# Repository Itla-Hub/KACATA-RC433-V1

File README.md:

# KACATA-RC433-V1
KACATA-RC433-V1 es un control remoto a 433Mhz
MCU MKE04Z128VQH4

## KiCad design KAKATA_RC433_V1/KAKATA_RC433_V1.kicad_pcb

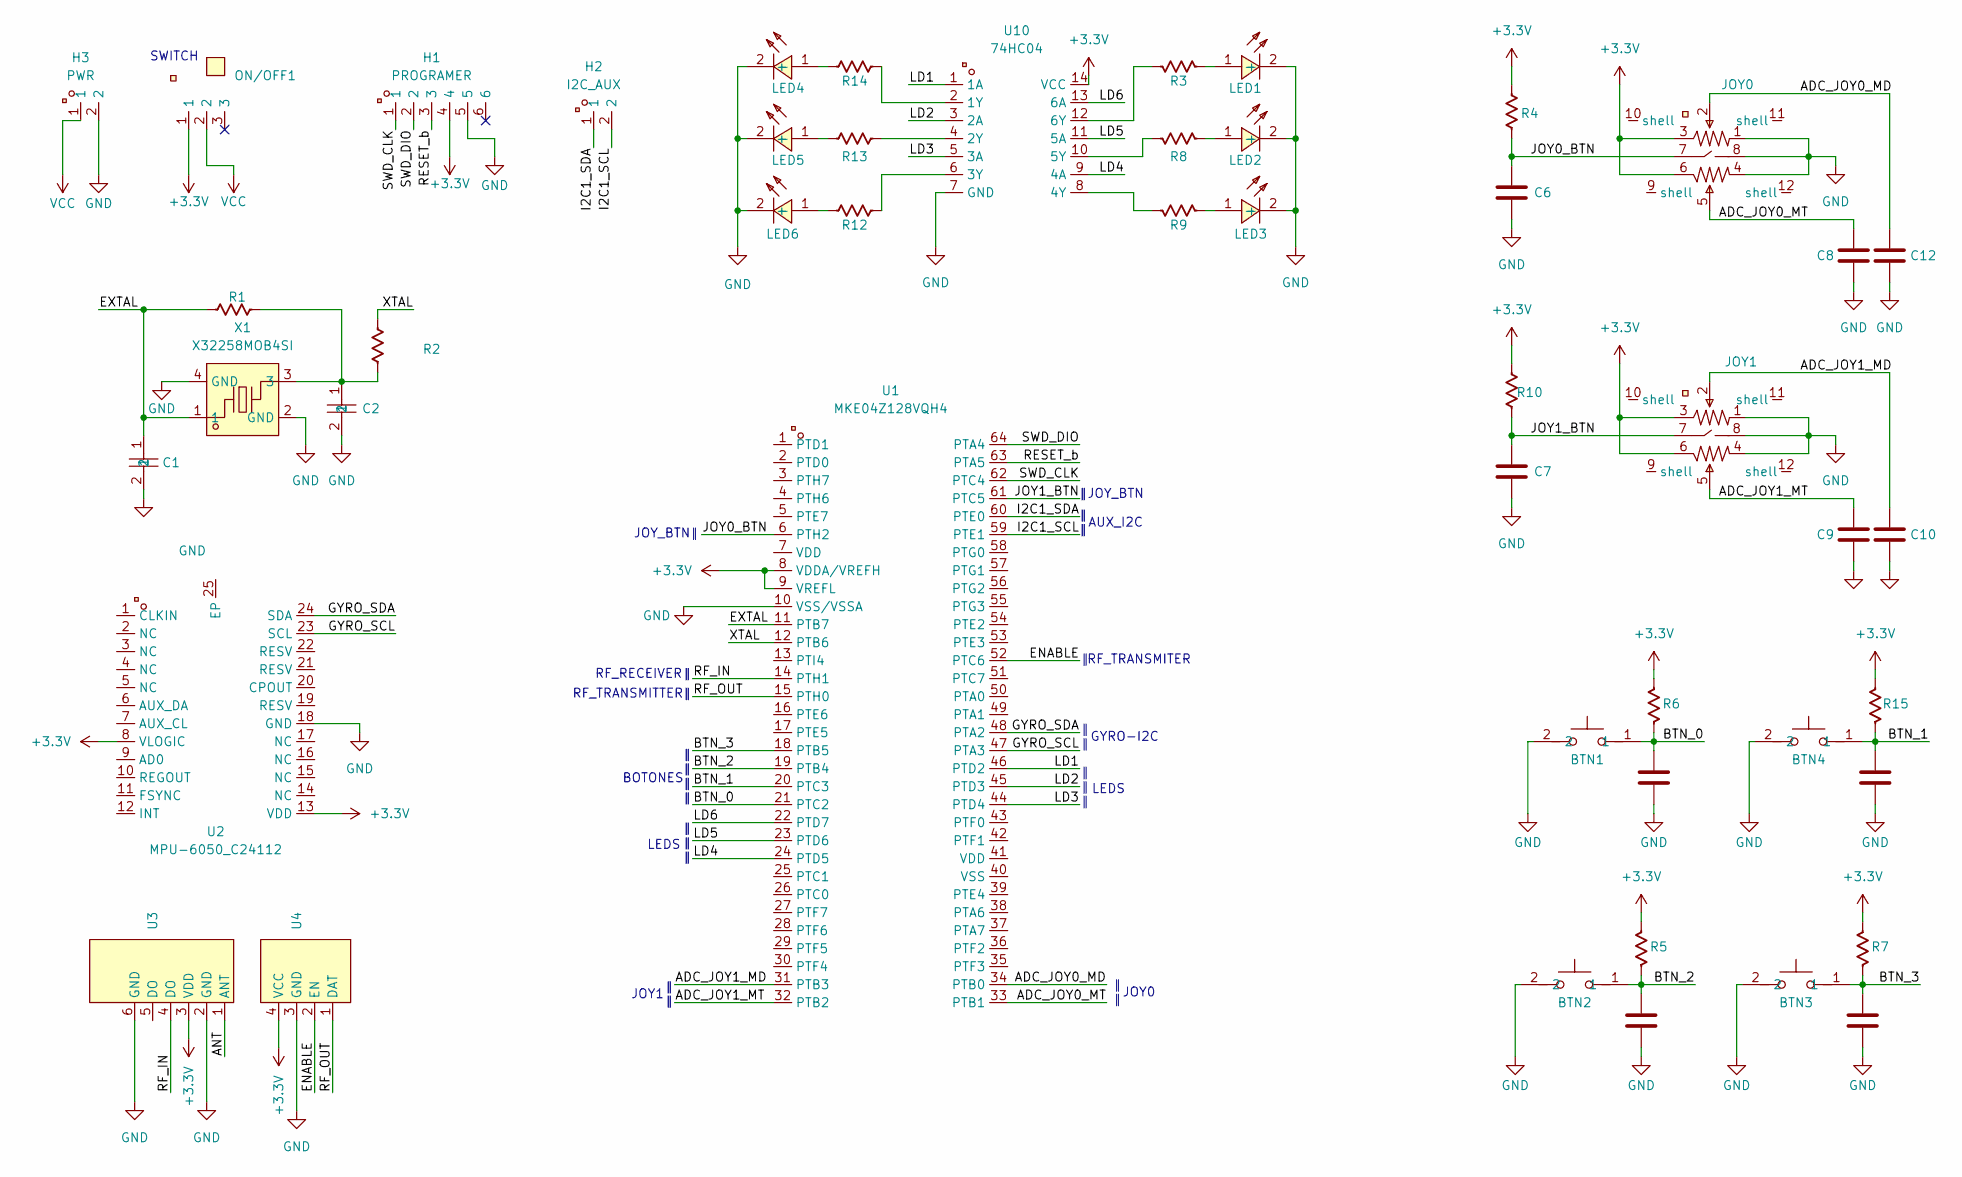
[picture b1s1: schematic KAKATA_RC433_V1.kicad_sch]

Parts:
BTN1, BTN2, BTN3, BTN4: CPG151101D01; SW-TH_CPG151101D9X; LCSC Part C49234238
C1, C2: CL10C120JB8NNNC; C0603; LCSC Part C38523
C3, C4, C5, C6, C7, C8, C9, C10, C11, C12: C_0603; C_0603_1608Metric
H1: PROGRAMER; HDR-TH_6P-P2.54-V-M; LCSC Part C42431790
H2: I2C_AUX; HDR-TH_2P-P2.54-V-M; LCSC Part C42431820
H3: PWR; HDR-TH_2P-P2.54-V-M; LCSC Part C42431820
JOY0, JOY1: YF16S-FL7.2-B5KB(45-10)-Y; JOYTICK-TH_YF16S-FL7.2-B5KB-45-10-Y_1; LCSC Part C37323740
LED1, LED2, LED3, LED4, LED5, LED6: YLED0603R; LED0603-FD; LCSC Part C19171390
ON/OFF1: MT-0-123-D001-D000-LF; SW-TH_3P-L13.1-W8.0-P4.70_MT-0-102-F001-T000-RS; LCSC Part C22448935
R1, R2, R3, R4, R5, R6, R7, R8, R9, R10, R12, R13, R14, R15: R_0603; R_0603_1608Metric
U1: MKE04Z128VQH4; QFP-64_L14.0-W14.0-P0.80-LS17.2-BL; LCSC Part C1340193
U2: MPU-6050_C24112; QFN-24_L4.0-W4.0-P0.50-BL-EP2.7; LCSC Part C24112
U3: 433 MHz RF RECEIVER; rf_433mhz_receiver
U4: 433 MHz TRANSMITTER; RF_433MHz_transmisor
U10: 74HC04; SOIC-14_L8.7-W3.9-P1.27-LS6.0-BL; LCSC Part C86613
X1: X32258MOB4SI; CRYSTAL-SMD_4P-L3.2-W2.5-BL; LCSC Part C2682775

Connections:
+3.3V: H1.4, JOY0.3, JOY0.6, JOY1.3, JOY1.6, ON/OFF1.1, R4.1, R5.1, R6.1, R7.1, R10.1, R15.1, U1.8 (VDDA/VREFH), U1.9 (VREFL), U2.8 (VLOGIC), U2.13 (VDD), U3.3 (VDD), U4.4 (VCC), U10.14 (VCC)
/ADC_JOY0_MD: C12.1, JOY0.2, U1.34 (PTB0)
/ADC_JOY0_MT: C8.1, JOY0.5, U1.33 (PTB1)
/ADC_JOY1_MD: C10.1, JOY1.2, U1.31 (PTB3)
/ADC_JOY1_MT: C9.1, JOY1.5, U1.32 (PTB2)
/ANT: U3.1 (ANT)
/BTN_0: BTN1.1, C4.1, R6.2, U1.21 (PTC2)
/BTN_1: BTN4.1, C11.1, R15.2, U1.20 (PTC3)
/BTN_2: BTN2.1, C3.1, R5.2, U1.19 (PTB4)
/BTN_3: BTN3.1, C5.1, R7.2, U1.18 (PTB5)
/ENABLE: U1.52 (PTC6), U4.2 (EN)
/EXTAL: C1.1, R1.1, U1.11 (PTB7), X1.1
/GYRO_SCL: U1.47 (PTA3), U2.23 (SCL)
/GYRO_SDA: U1.48 (PTA2), U2.24 (SDA)
/I2C1_SCL: H2.2, U1.59 (PTE1)
/I2C1_SDA: H2.1, U1.60 (PTE0)
/JOY0_BTN: C6.1, JOY0.7, R4.2, U1.6 (PTH2)
/JOY1_BTN: C7.1, JOY1.7, R10.2, U1.61 (PTC5)
/LD1: U1.46 (PTD2), U10.1 (1A)
/LD2: U1.45 (PTD3), U10.3 (2A)
/LD3: U1.44 (PTD4), U10.5 (3A)
/LD4: U1.24 (PTD5), U10.9 (4A)
/LD5: U1.23 (PTD6), U10.11 (5A)
/LD6: U1.22 (PTD7), U10.13 (6A)
/RESET_b: H1.3, U1.63 (PTA5)
/RF_IN: U1.14 (PTH1), U3.4 (DO)
/RF_OUT: U1.15 (PTH0), U4.1 (DAT)
/SWD_CLK: H1.1, U1.62 (PTC4)
/SWD_DIO: H1.2, U1.64 (PTA4)
/XTAL: R2.2, U1.12 (PTB6)
GND: BTN1.2, BTN2.2, BTN3.2, BTN4.2, C1.2, C2.2, C3.2, C4.2, C5.2, C6.2, C7.2, C8.2, C9.2, C10.2, C11.2, C12.2, H1.5, H3.2, JOY0.1, JOY0.4, JOY0.8, JOY1.1, JOY1.4, JOY1.8, LED1.2 (-), LED2.2 (-), LED3.2 (-), LED4.2 (-), LED5.2 (-), LED6.2 (-), U1.10 (VSS/VSSA), U2.18 (GND), U3.2 (GND), U3.6 (GND), U4.3 (GND), U10.7 (GND), X1.2 (GND), X1.4 (GND)
unnamed: C2.1, R1.2, R2.1, X1.3
unnamed: LED1.1 (+), R3.1
unnamed: LED2.1 (+), R8.1
unnamed: LED3.1 (+), R9.1
unnamed: LED4.1 (+), R14.1
unnamed: LED5.1 (+), R13.1
unnamed: LED6.1 (+), R12.1
unnamed: R14.2, U10.2 (1Y)
unnamed: R13.2, U10.4 (2Y)
unnamed: R12.2, U10.6 (3Y)
unnamed: R9.2, U10.8 (4Y)
unnamed: R8.2, U10.10 (5Y)
unnamed: R3.2, U10.12 (6Y)
VCC: H3.1, ON/OFF1.2

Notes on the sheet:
RF_TRANSMITTER
SWITCH
LEDS
‖ ‖
BOTONES
‖ ‖ ‖
RF_RECEIVER
‖ ‖ ‖ ‖
‖ ‖
GYRO-I2C
RF_TRANSMITER
JOY_BTN
JOY1
AUX_I2C
JOY0

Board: 4 copper layers, 48 parts (0 on the bottom side), 44 nets, no tracks yet.

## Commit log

2025-11-28 Add MCU information to README
2025-11-30 Primer commit
